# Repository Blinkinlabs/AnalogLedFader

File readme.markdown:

Analog LED Fader

An Arduino-compatible, DMX-like analog LED controller

Our VID/PID: 0x1d50/0x605e

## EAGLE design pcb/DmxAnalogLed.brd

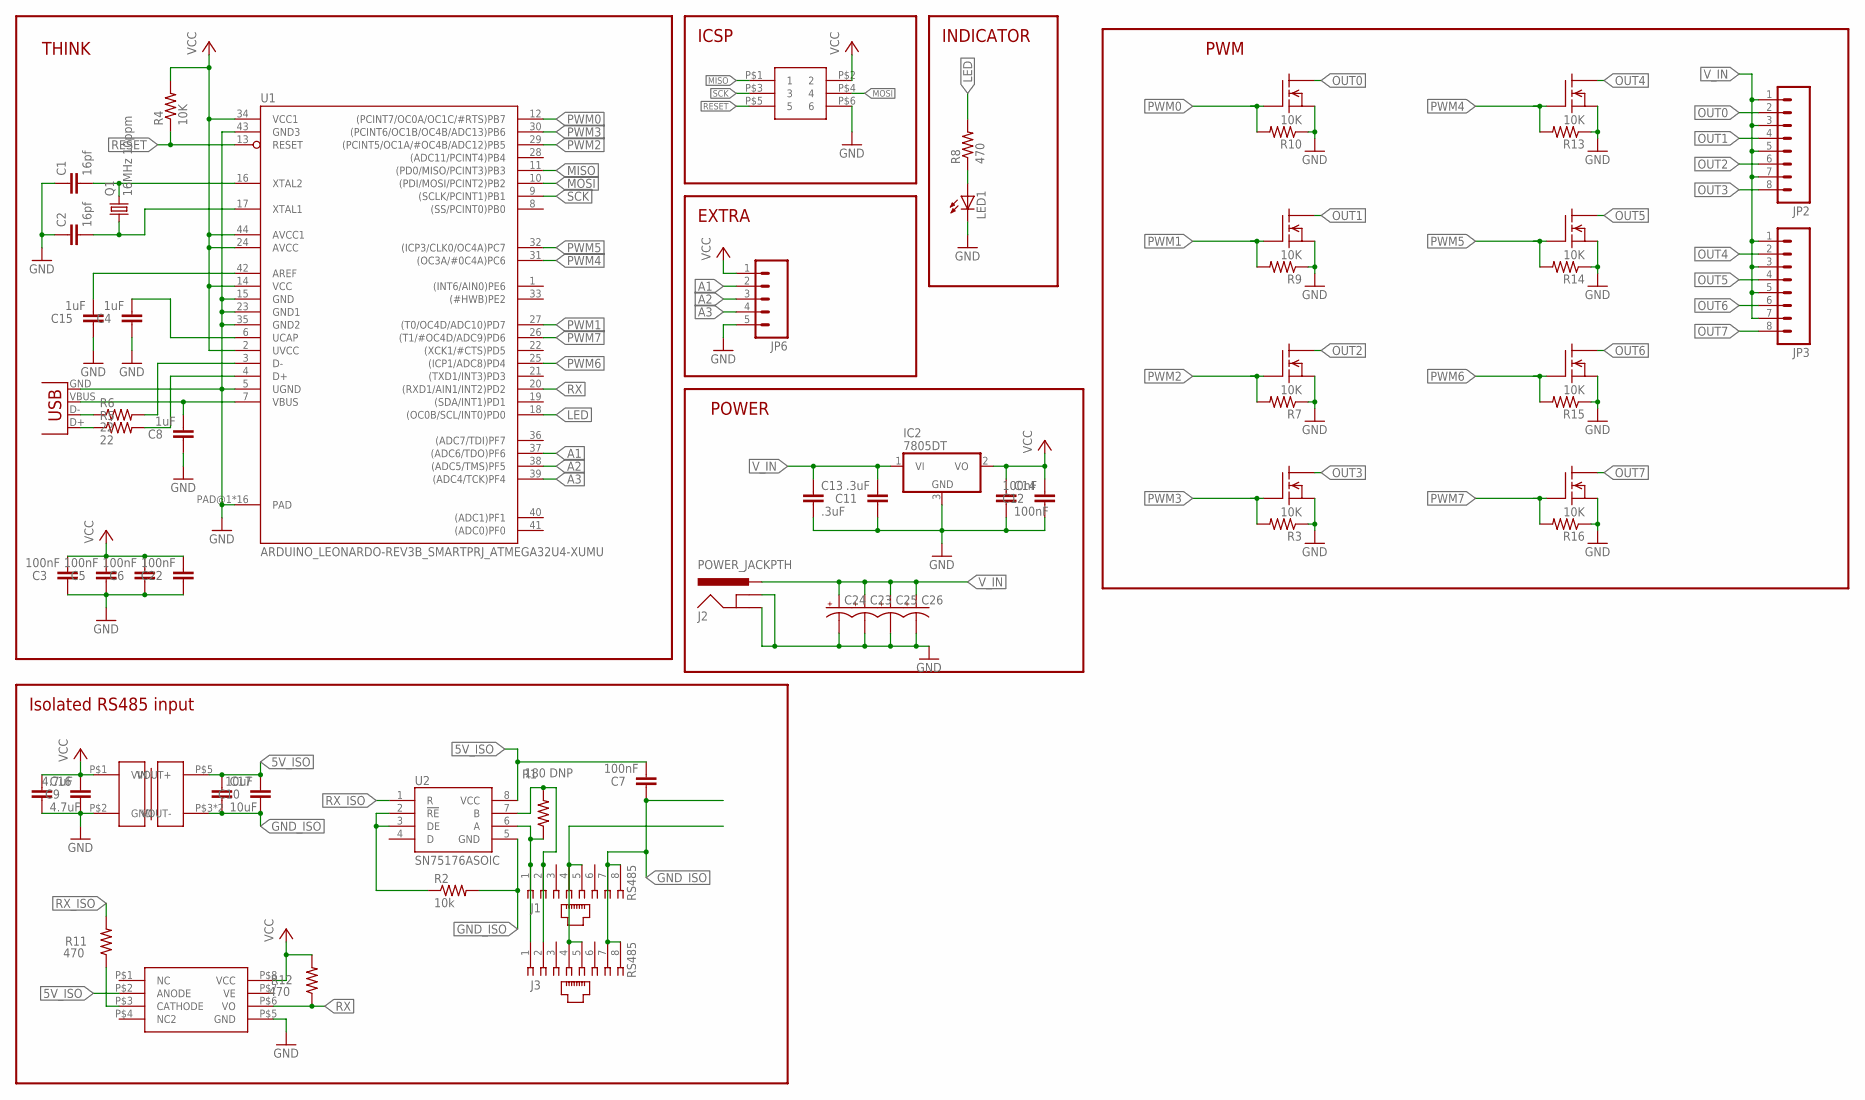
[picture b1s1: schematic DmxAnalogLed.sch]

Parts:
C1, C2: 16pf; 0805
C3, C5, C6, C7, C12, C22: 100nF; 0805
C4, C8, C15: 1uF; 0805
C9: 4.7uF; 0805
C10: 10uF; 0805
C11: .3uF; 0805
C13: .3uF; 1210
C14: 100nF; 1210
C16: 4.7uF; 1210
C17: 10uF; 1210
C23, C24, C25, C26: CAP_POLE; PANASONIC_E
IC2: 7805DT; TO252
J1, J3: RS485; 520426-4
J2: POWER_JACKPTH; POWER_JACK_PTH
JP2, JP3: M083.5MM-8; SCREWTERMINAL-3.5MM-8
JP6: M05PTH; 1X05
LED1: LED5MM
Q1: 16MHz 10ppm; XS3225
R1: 180 DNP; 0805
R2: 10k; 0805
R3, R4, R7, R9, R10, R13, R14, R15, R16: 10K; 0805
R5, R6: 22; 0805
R8, R11, R12: 470; 0805
U1: ARDUINO_LEONARDO-REV3B_SMARTPRJ_ATMEGA32U4-XUMU; ARDUINO_LEONARDO-REV3B_SMARTPRJ_QFN44ML7X7
U2: SN75176ASOIC; SO08
U$1, U$3, U$4, U$5, U$6, U$7, U$8, U$9: N_MOSFET; TO252
U$2: 2X3HEADER
U$10: DC_DC_ISOLATED_0505; IB_XLS-1W
U$12: 6N137; 8_SOIC
X1: USBPTH; USB-B-PTH

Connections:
5V_ISO: C7.2, C10.2, C17.1, U2.8 (VCC), U$10.P$5 (VOUT+), U$12.P$2 (ANODE)
A1: JP6.2, U1.37 ((ADC6/TDO)PF6)
A2: JP6.3, U1.38 ((ADC5/TMS)PF5)
A3: JP6.4, U1.39 ((ADC4/TCK)PF4)
CONNECT_ME: R2.1, U2.2 (!RE), U2.3 (DE)
GND: C1.1, C2.1, C3.1, C4.1, C5.1, C6.1, C8.1, C9.1, C11.1, C12.1, C13.2, C14.2, C15.1, C16.2, C22.1, C23.-, C24.-, C25.-, C26.-, IC2.3 (GND), J2.GND, J2.GNDBREAK, JP6.5, LED1.K (C), R3.1, R7.1, R9.1, R10.1, R13.1, R14.1, R15.1, R16.1, U1.5 (UGND), U1.15 (GND), U1.23 (GND1), U1.35 (GND2), U1.43 (GND3), U1.PAD@1 (PAD), U1.PAD@2 (PAD), U1.PAD@3 (PAD), U1.PAD@4 (PAD), U1.PAD@5 (PAD), U1.PAD@6 (PAD), U1.PAD@7 (PAD), U1.PAD@8 (PAD), U1.PAD@9 (PAD), U1.PAD@10 (PAD), U1.PAD@11 (PAD), U1.PAD@12 (PAD), U1.PAD@13 (PAD), U1.PAD@14 (PAD), U1.PAD@15 (PAD), U1.PAD@16 (PAD), U$1.P$2 (S), U$2.P$6 (6), U$3.P$2 (S), U$4.P$2 (S), U$5.P$2 (S), U$6.P$2 (S), U$7.P$2 (S), U$8.P$2 (S), U$9.P$2 (S), U$10.P$2 (GND), U$12.P$5 (GND), X1.GND
GND_ISO: C7.1, C10.1, C17.2, J1.7, J1.8, J3.7, J3.8, R2.2, U2.5 (GND), U$10.P$3 (VOUT-), U$10.P$4 (VOUT-)
LED: R8.2, U1.18 ((OC0B/SCL/INT0)PD0)
MISO: U1.11 ((PD0/MISO/PCINT3)PB3), U$2.P$1 (1)
MOSI: U1.10 ((PDI/MOSI/PCINT2)PB2), U$2.P$4 (4)
unnamed: R6.1, X1.D-
unnamed: C1.2, Q1.P$3 (2), U1.16 (XTAL2)
unnamed: R5.1, X1.D+
unnamed: R5.2, U1.4 (D+)
unnamed: C2.2, Q1.P$1 (1), U1.17 (XTAL1)
unnamed: R6.2, U1.3 (D-)
unnamed: LED1.A, R8.1
unnamed: C4.2, U1.6 (UCAP)
unnamed: C8.2, U1.7 (VBUS), X1.VBUS
unnamed: C15.2, U1.42 (AREF)
unnamed: R11.1, U$12.P$3 (CATHODE)
OUT0: JP2.2, U$1.P$3 (D)
OUT1: JP2.4, U$3.P$3 (D)
OUT2: JP2.6, U$4.P$3 (D)
OUT3: JP2.8, U$5.P$3 (D)
OUT4: JP3.2, U$6.P$3 (D)
OUT5: JP3.4, U$7.P$3 (D)
OUT6: JP3.6, U$8.P$3 (D)
OUT7: JP3.8, U$9.P$3 (D)
PWM0: R10.2, U1.12 ((PCINT7/OC0A/OC1C/#RTS)PB7), U$1.P$1 (G)
PWM1: R9.2, U1.27 ((T0/OC4D/ADC10)PD7), U$3.P$1 (G)
PWM2: R7.2, U1.29 ((PCINT5/OC1A/#OC4B/ADC12)PB5), U$4.P$1 (G)
PWM3: R3.2, U1.30 ((PCINT6/OC1B/OC4B/ADC13)PB6), U$5.P$1 (G)
PWM4: R13.2, U1.31 ((OC3A/#0C4A)PC6), U$6.P$1 (G)
PWM5: R14.2, U1.32 ((ICP3/CLK0/OC4A)PC7), U$7.P$1 (G)
PWM6: R15.2, U1.25 ((ICP1/ADC8)PD4), U$8.P$1 (G)
PWM7: R16.2, U1.26 ((T1/#OC4D/ADC9)PD6), U$9.P$1 (G)
RESET: R4.1, U1.13 (RESET), U$2.P$5 (5)
RS485A: J1.1, J3.1, R1.1, U2.6 (A)
RS485B: J1.2, J3.2, R1.2, U2.7 (B)
RX: R12.1, U1.20 ((RXD1/AIN1/INT2)PD2), U$12.P$6 (VO)
RX_ISO: R11.2, U2.1 (R)
SCK: U1.9 ((SCLK/PCINT1)PB1), U$2.P$3 (3)
VCC: C3.2, C5.2, C6.2, C9.2, C12.2, C14.1, C16.1, C22.2, IC2.2 (VO), JP6.1, R4.2, R12.2, U1.2 (UVCC), U1.14 (VCC), U1.24 (AVCC), U1.34 (VCC1), U1.44 (AVCC1), U$2.P$2 (2), U$10.P$1 (VIN), U$12.P$8 (VCC)
VMOT: J1.4, J1.5, J3.4, J3.5
V_IN: C11.2, C13.1, C23.+, C24.+, C25.+, C26.+, IC2.1 (VI), J2.PWR, JP2.1, JP2.3, JP2.5, JP2.7, JP3.1, JP3.3, JP3.5, JP3.7

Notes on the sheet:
Isolated RS485 input
ICSP
INDICATOR
EXTRA
PWM
POWER
THINK

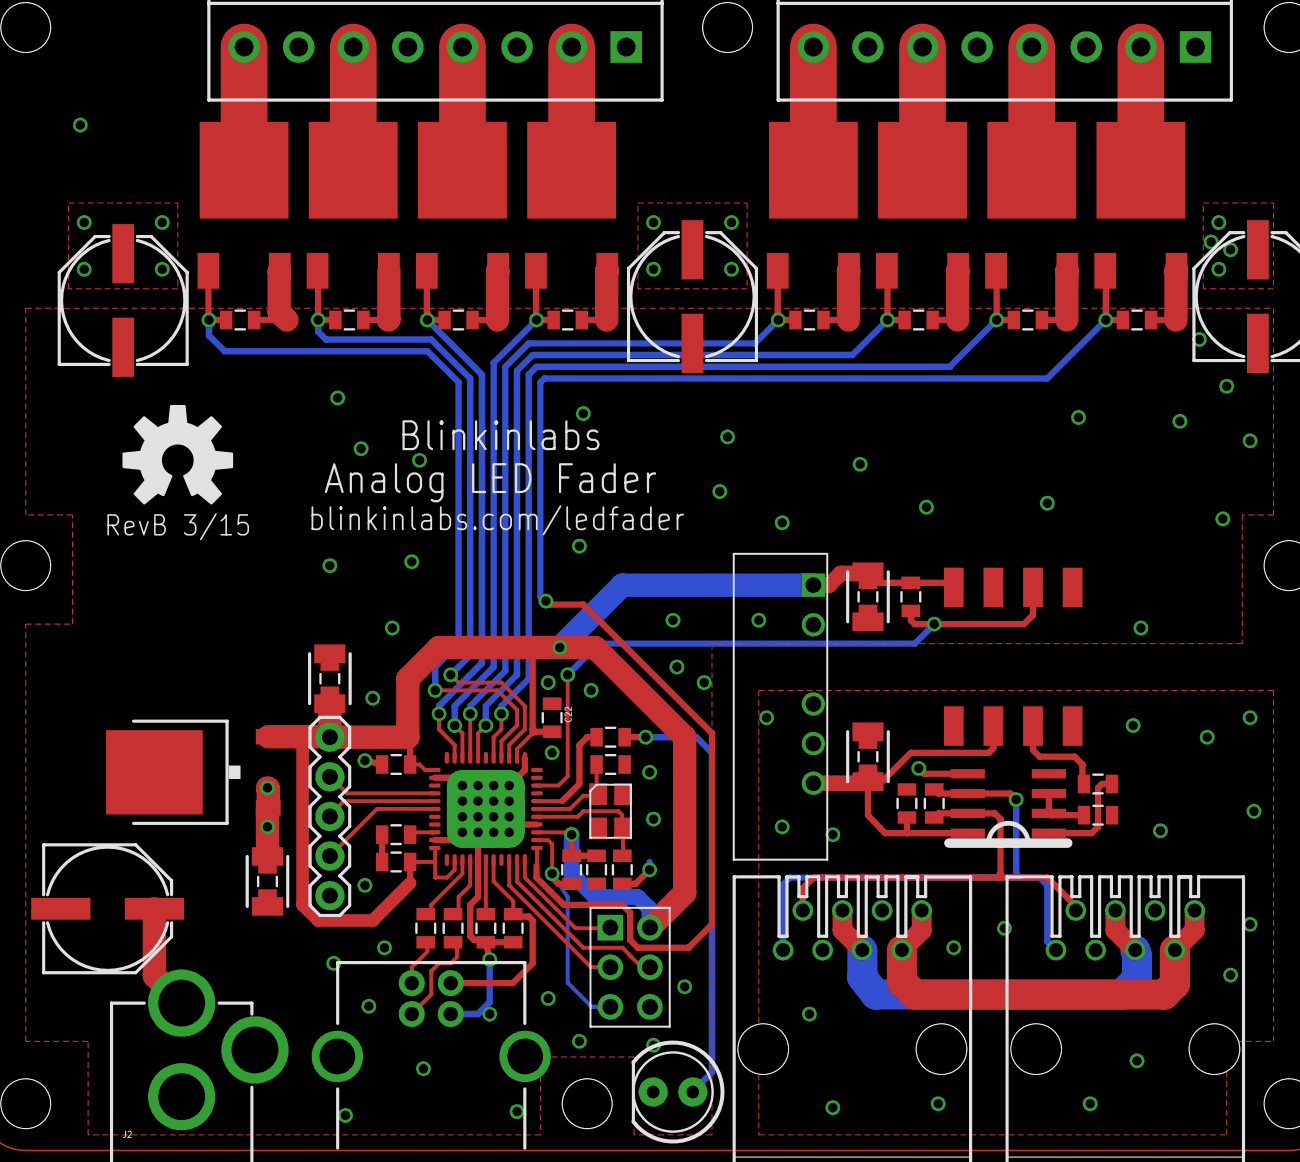
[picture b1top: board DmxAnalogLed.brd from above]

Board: 2 copper layers, 62 parts (0 on the bottom side), 46 nets.

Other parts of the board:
U$13: OSHW-LOGO-L

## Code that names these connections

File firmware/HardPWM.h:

#ifndef _HARD_PWM_h
#define _HARD_PWM_h

#include <Arduino.h>

// Number of PWM outputs enabled
#define pwmCount  6 

// This is an alternate PWM interface for Arduino/Atmega32u4, that provides 488Hz,
// 14 or 10-bit PWM on the following outputs:
//
// PB7 (PWM0) (14 bit)
// PD7 (PWM1) (10 bit)
// PB5 (PWM2) (14 bit)
// PB6 (PWM3) (14 bit)
// PC6 (PWM4) (14 bit)
// PC7 (PWM5) (10 bit)
class HardPWM {
 private:
  uint16_t m_pwmValues[pwmCount];  // currrent logarithmic PWM setting for each PWM output

 public:
  // Start the software PWM driver. Initializes all outputs,
  // and starts the timer.
  void begin();
  
  // Set the value of an output pin
  // @param channel PWM output channel to update
  // @param value New output value (0-1024)
  void write(uint8_t channel, uint16_t value);
  
  // Read the value of an output pin
  // @param channel PWM output channel to read
  // @return value Channel value (0-1024)
  uint16_t read(uint8_t channel);
};

#endif

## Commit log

2013-01-07 DMX Analog LED is a control board for 8 or 16 channels of analog LED chains.
    Each output is spec'd to 3A at 12V.
2013-01-08 Add isolated RS485 circuit, begin transistor layout
2013-01-10 Board update
2013-02-01 Remove PWM chip, start routing board
2013-02-01 Start laying out board
2013-02-02 Routed, pending review
2013-02-06 Add pwm test firmware
2013-02-06 Software PWM @325Hz. Has stability issues on the low end
2013-02-06 Add simple serial packet decoder, processing example
2013-02-07 Improve minimum on time to achieve darker levels.
2013-02-07 Last ditch: unroll stepping loop for short duration PWM. It's still a bit too unstable.
2013-02-14 Re-wire PWMs for hardware PWM generation. Bugfix: Serial should be connected to AVR RX, not TX
2013-02-14 Almost ready for a re-release of RevA
2013-02-16 Switch to hardware PWM. Limited to 6 channels, but can run at 16KHz.
2013-02-16 Update firmware comments, add support for both usb/rs485 serial inputs
2013-02-16 Can control all 6 outputs, at 16 or 10 bit resolution
2013-03-01 Re-order Hardware PWM library to match the PCB
2013-03-01 Add extra drain vias, space for mounting holes, line up connectors, drop series gate resistors, fix RX line
2013-03-06 Release RevB
2013-03-08 Notes from the RevA boards
2013-03-08 Make the intervals bigger
2013-03-13 Make random mode fast
2013-03-13 Fix LED port
2013-03-13 Update component values on PCB
2013-03-13 Update TODOs
2013-03-14 Add License. This project is now Apache 2.0
2013-03-16 Get RevB ready
2013-03-16 RevB candidate; fixes ground plane, isolation, regulator placement, silk.
2013-03-25 Implement addressing in the firmware, add Disco Party processing example
2013-03-29 Firmware: reset all outputs to 0 on start. SerialDebugger: Output enough channels for a single board.
2013-03-29 Make the software faster.
2013-06-09 Update examples to work with 13 boards, fix bugs that caused the serial formatting to be incorrect, fix the firmware!
2013-06-10 More protocol updates: now implement CRC
2013-10-07 Name change
2013-10-07 Change library name, too
2013-10-07 Rename board, too!
2014-01-29 Update LICENSE.md
    Final time to muck this one up :-P. The code examples are meant to be under MIT.
